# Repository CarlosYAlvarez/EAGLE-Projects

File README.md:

# EAGLE-Projects
Personal EAGLE Projects

# SimpleDuino
Arduino circuit on breadboard version.
References: https://circuitdigest.com/microcontroller-projects/how-to-burn-bootloader-in-atmega328p-and-program-using-arduino-ide

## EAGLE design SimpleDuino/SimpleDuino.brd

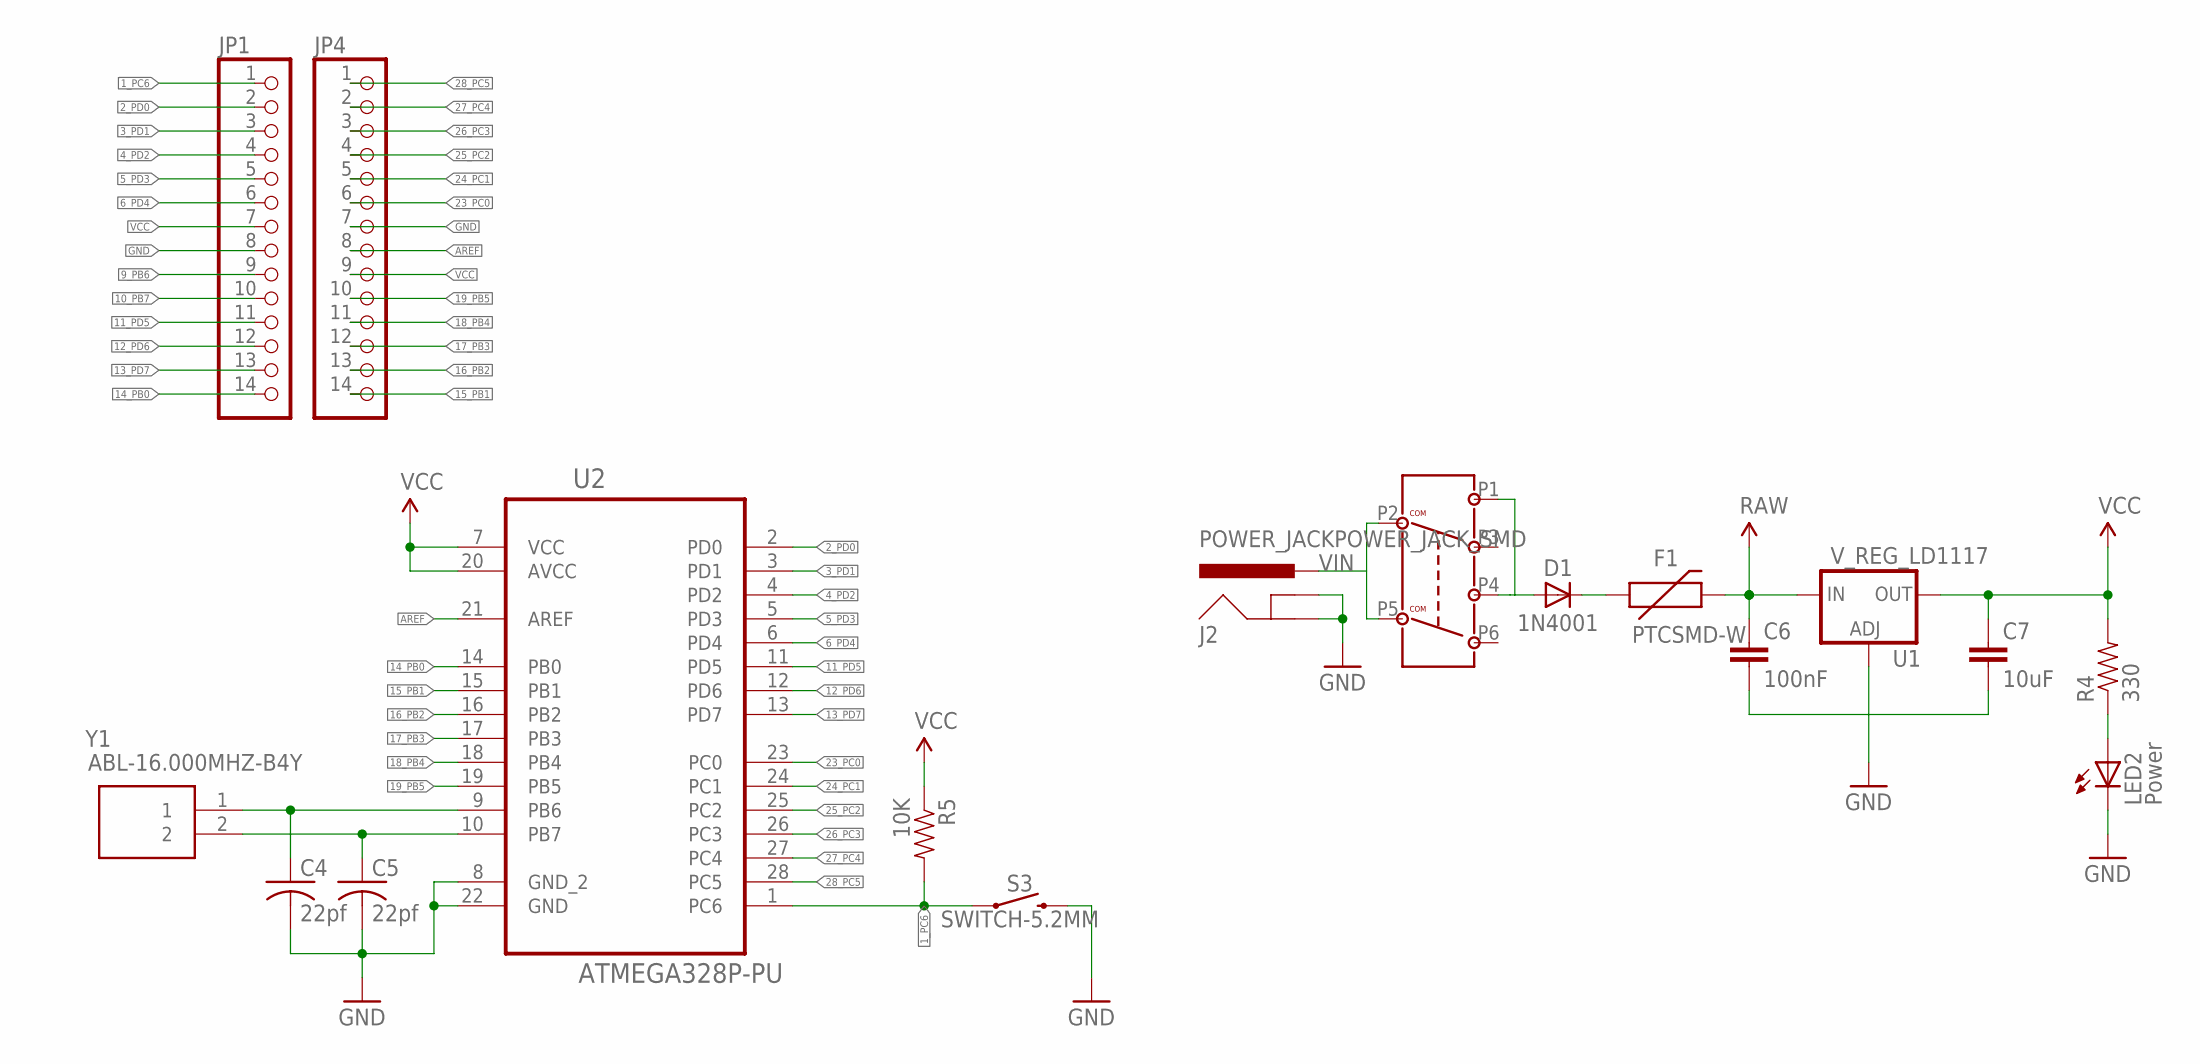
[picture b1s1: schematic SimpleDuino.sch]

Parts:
C4, C5: 22pf; C0805
C6: 100nF; 0603-CAP
C7: 10uF; 0603-CAP
D1: 1N4001; DO41-10
F1: PTCSMD-W; PTC-1206-WIDE
J2: POWER_JACKPOWER_JACK_SMD; POWER_JACK_SMD
JP1, JP4: PINHD-1X14; 1X14
LED2: Power; LED-1206
POWER_SWITCH: 6-PIN-SLIDE-SWITCH
R4: 330; 0603-RES
R5: 10K; 0603-RES
S3: SWITCH-5.2MM; TACTILE_SWITCH_SMD_5.2MM
U1: V_REG_LD1117; SOT223
U2: ATMEGA328P-PU; DIP254P762X457-28
Y1: ABL-16.000MHZ-B4Y; HC/49US_(AT49)PTH

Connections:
1_PC6: JP1.1, R5.2, S3.1, U2.1 (PC6)
2_PD0: JP1.2, U2.2 (PD0)
3_PD1: JP1.3, U2.3 (PD1)
4_PD2: JP1.4, U2.4 (PD2)
5_PD3: JP1.5, U2.5 (PD3)
6_PD4: JP1.6, U2.6 (PD4)
9_PB6: C4.1, JP1.9, U2.9 (PB6), Y1.1
10_PB7: C5.1, JP1.10, U2.10 (PB7), Y1.2
11_PD5: JP1.11, U2.11 (PD5)
12_PD6: JP1.12, U2.12 (PD6)
13_PD7: JP1.13, U2.13 (PD7)
14_PB0: JP1.14, U2.14 (PB0)
15_PB1: JP4.14, U2.15 (PB1)
16_PB2: JP4.13, U2.16 (PB2)
17_PB3: JP4.12, U2.17 (PB3)
18_PB4: JP4.11, U2.18 (PB4)
19_PB5: JP4.10, U2.19 (PB5)
23_PC0: JP4.6, U2.23 (PC0)
24_PC1: JP4.5, U2.24 (PC1)
25_PC2: JP4.4, U2.25 (PC2)
26_PC3: JP4.3, U2.26 (PC3)
27_PC4: JP4.2, U2.27 (PC4)
28_PC5: JP4.1, U2.28 (PC5)
AREF: JP4.8, U2.21 (AREF)
GND: C4.2, C5.2, C6.2, C7.2, J2.GND, J2.P$4 (GNDBREAK), JP1.8, JP4.7, LED2.C, S3.3 (2), U1.1 (ADJ), U2.8 (GND_2), U2.22 (GND)
unnamed: D1.C, F1.1
unnamed: LED2.A, R4.1
unnamed: D1.A, POWER_SWITCH.P1 (1), POWER_SWITCH.P4 (4)
RAW: C6.1, F1.2, U1.3 (IN)
VCC: C7.1, JP1.7, JP4.9, R4.2, R5.1, U1.2 (OUT), U2.7 (VCC), U2.20 (AVCC)
VIN: J2.VIN0 (PWR), POWER_SWITCH.P2 (2), POWER_SWITCH.P5 (5)

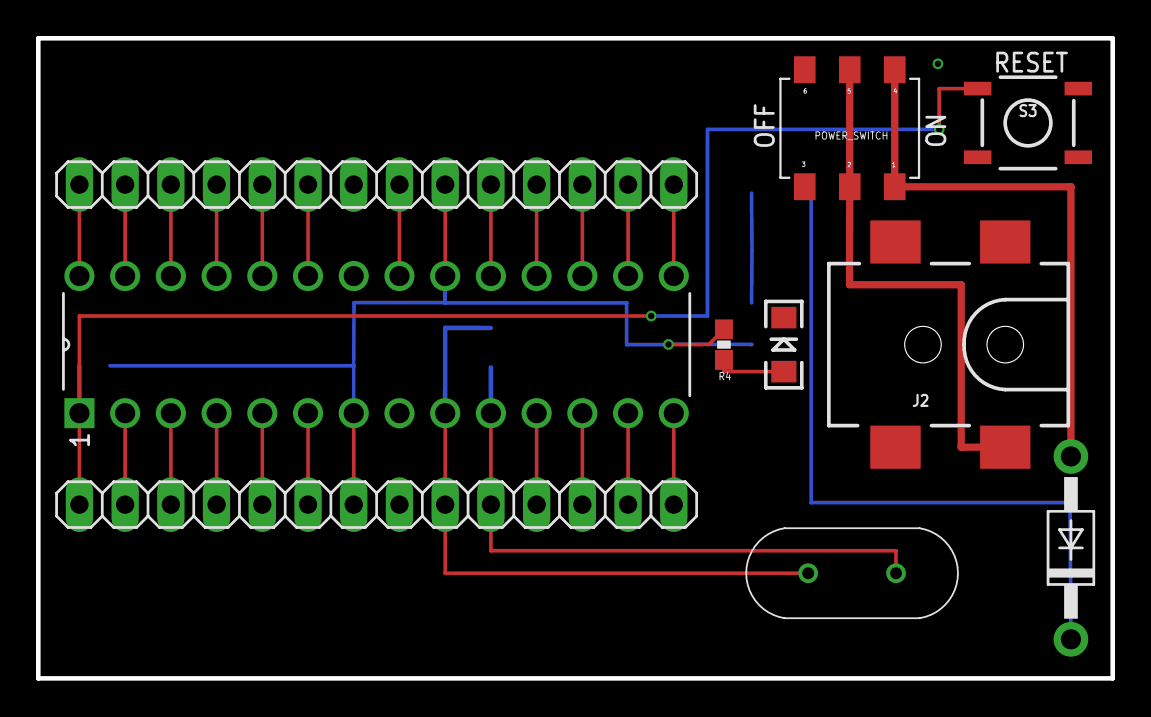
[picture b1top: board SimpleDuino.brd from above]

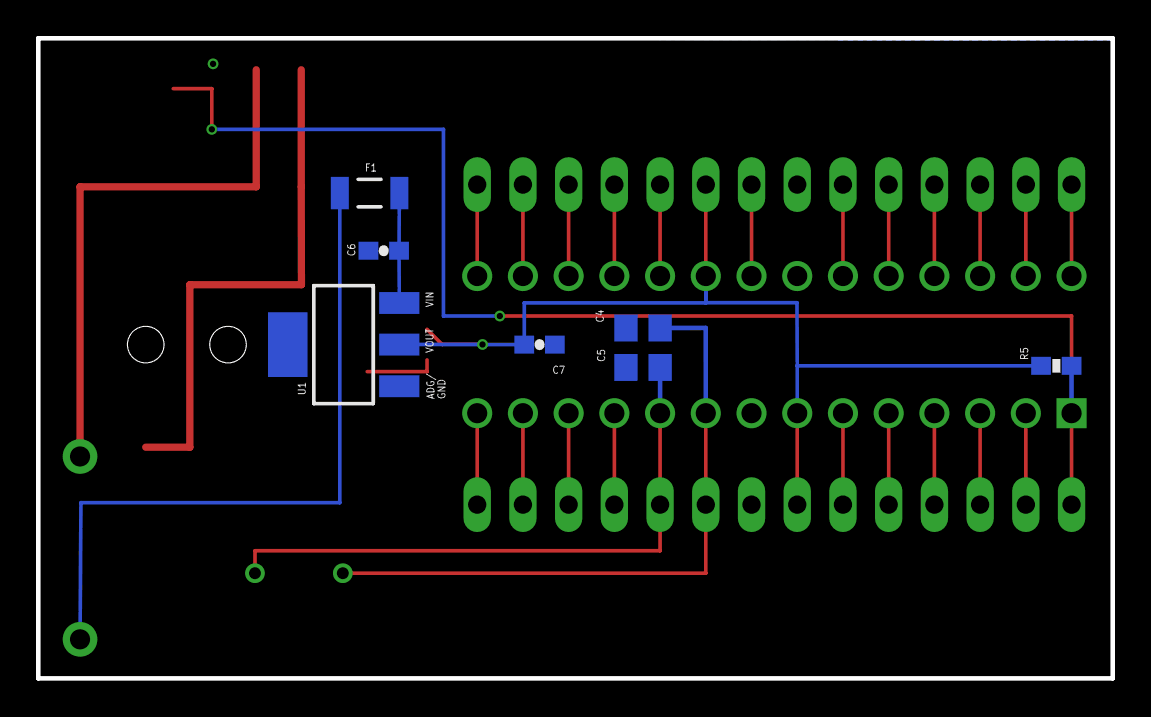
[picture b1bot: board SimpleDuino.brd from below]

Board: 2 copper layers, 59.7 x 35.6 mm, 17 parts (7 on the bottom side), 31 nets.

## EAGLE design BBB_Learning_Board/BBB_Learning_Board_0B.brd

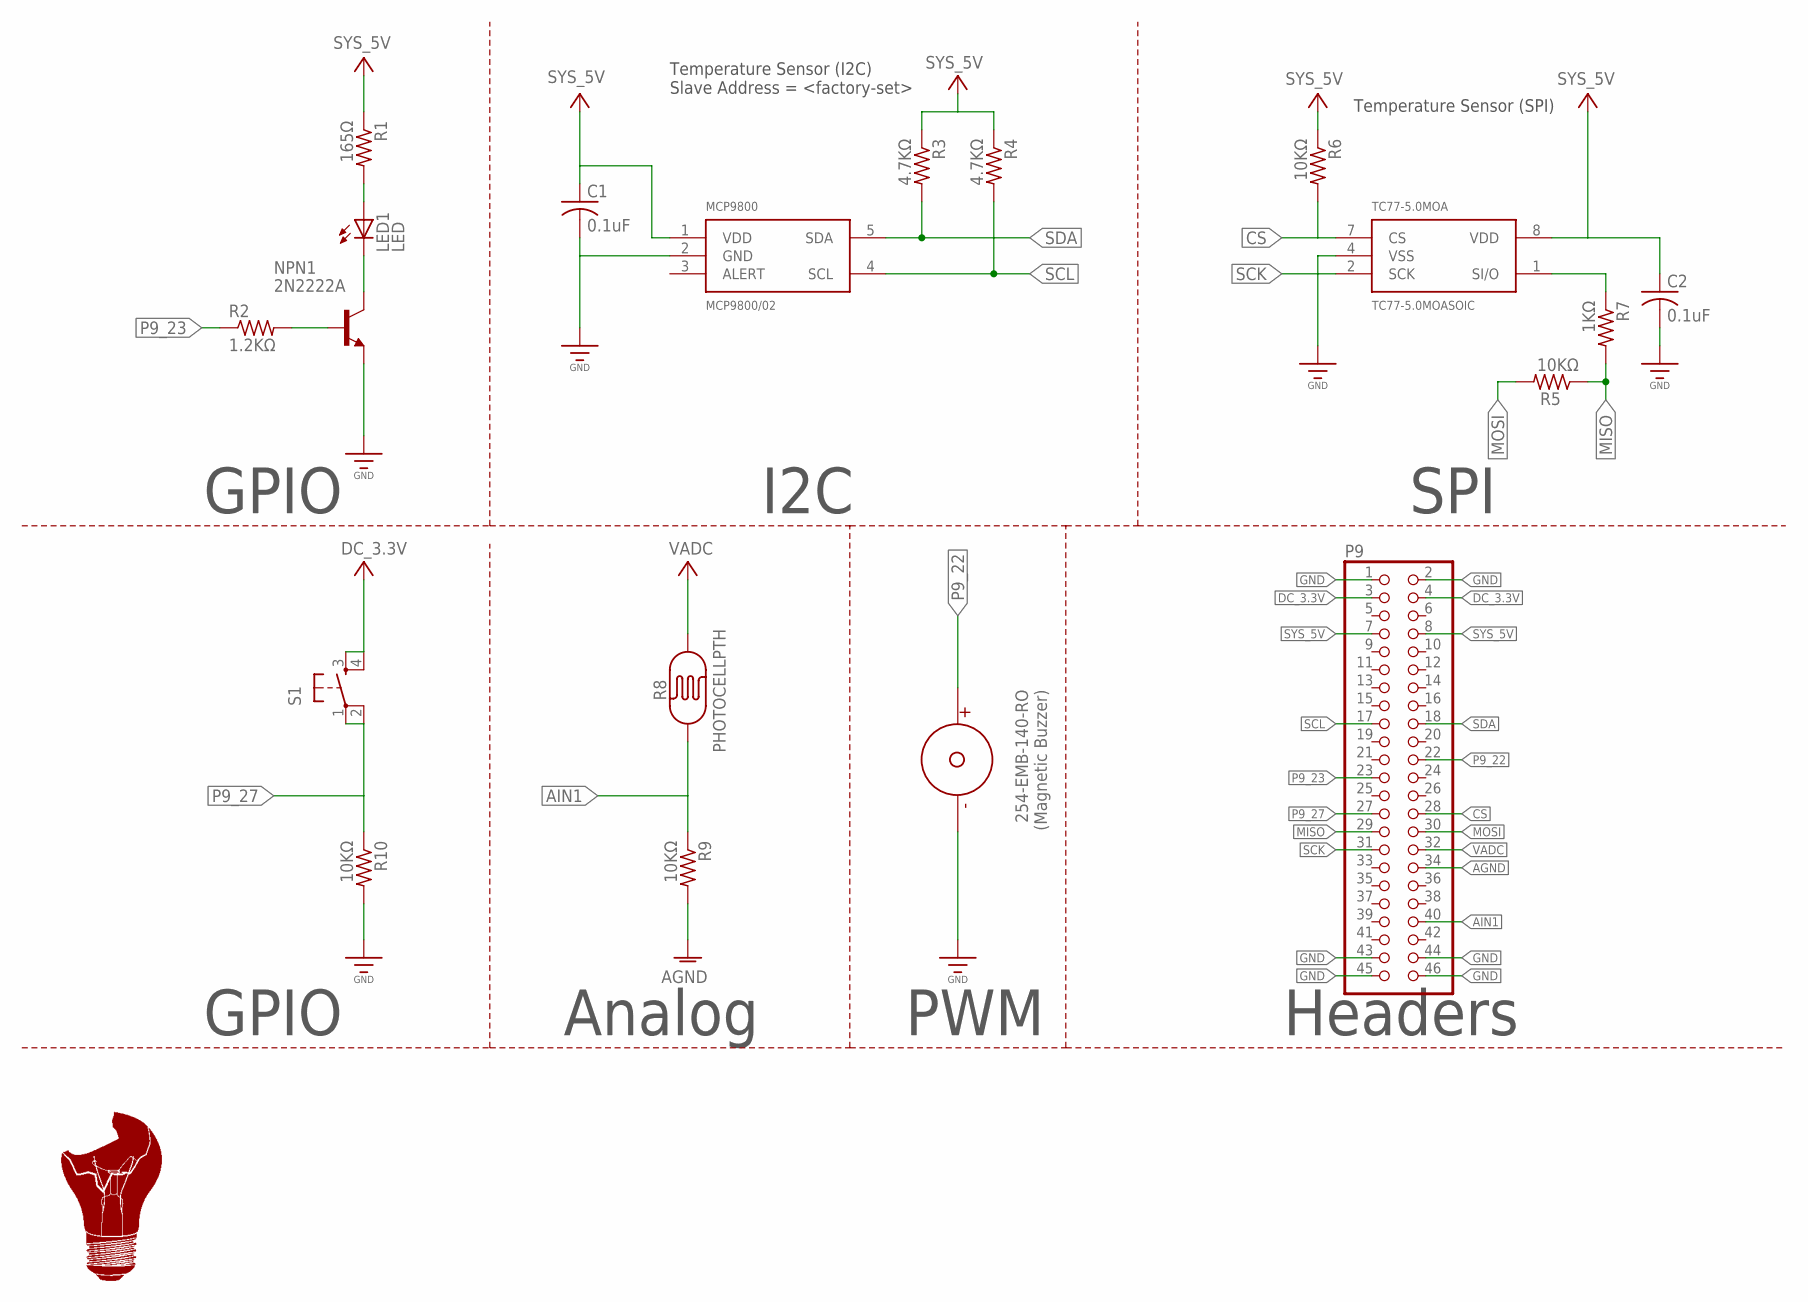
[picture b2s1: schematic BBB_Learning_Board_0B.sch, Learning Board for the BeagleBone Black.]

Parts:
C1, C2: 0.1uF; C0805
LED1: LED; LED5MM
MCP9800: MCP9800/02; SOT23-5
NPN1: 2N2222A; PINHD-1X3
P9: PINHD-2X23; 2X23
R1: 165Ω; R0805
R2: 1.2KΩ; R0805
R3, R4: 4.7KΩ; R0805
R5, R6, R9, R10: 10KΩ; R0805
R7: 1KΩ; R0805
R8: PHOTOCELLPTH; PHOTOCELL
S1: TAC_SWITCHPTH; TACTILE-PTH
TC77-5.0MOA: TC77-5.0MOASOIC; SOIC-8
U$6: 254-EMB-140-RO
U$7: LIGHTBULB_LOGOBOTTOM; LIGHTBULB_LOGO_BOTTOM-2_54CM2

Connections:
AGND: P9.34, R9.2
AIN1: P9.40, R8.1, R9.1
CS: P9.28, R6.2, TC77-5.0MOA.7 (CS)
DC_3.3V: P9.3, P9.4, S1.3, S1.4
GND: C1.2, C2.2, MCP9800.2 (GND), NPN1.1 (E), P9.1, P9.2, P9.43, P9.44, P9.45, P9.46, R10.2, TC77-5.0MOA.4 (VSS), U$6.NEGATIVE
MISO: P9.29, R5.1, R7.2
MOSI: P9.30, R5.2
unnamed: LED1.ANODE (A), R1.2
unnamed: NPN1.2 (B), R2.2
unnamed: LED1.CATHODE (C), NPN1.3 (C)
P9_22: P9.22, U$6.POSITIVE
P9_23: P9.23, R2.1
P9_27: P9.27, R10.1, S1.1, S1.2
SCK: P9.31, TC77-5.0MOA.2 (SCK)
SCL: MCP9800.4 (SCL), P9.17, R4.2
SDA: MCP9800.5 (SDA), P9.18, R3.2
SI/O: R7.1, TC77-5.0MOA.1 (SI/O)
SYS_5V: C1.1, C2.1, MCP9800.1 (VDD), P9.7, P9.8, R1.1, R3.1, R4.1, R6.1, TC77-5.0MOA.8 (VDD)
VADC: P9.32, R8.2

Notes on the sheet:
Temperature Sensor (I2C) Slave Address = <factory-set>
Temperature Sensor (SPI)
GPIO
I2C
SPI
Analog
PWM
Headers

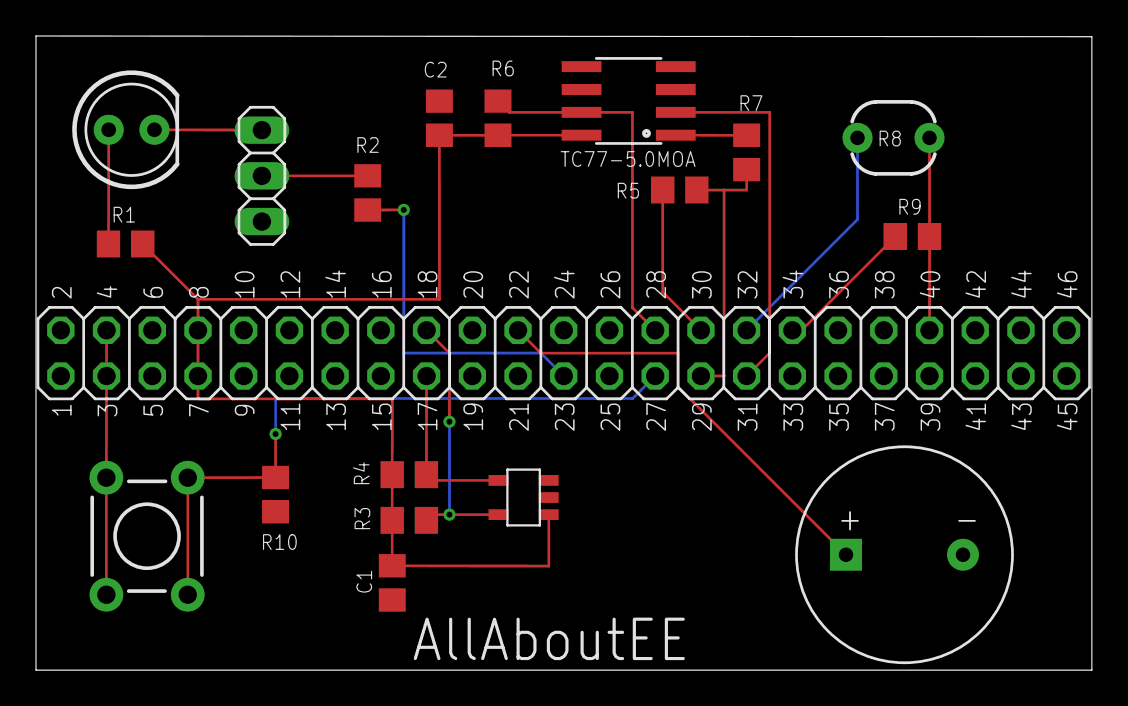
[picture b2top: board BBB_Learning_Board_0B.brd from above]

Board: 2 copper layers, 58.7 x 35.2 mm, 20 parts (0 on the bottom side), 19 nets.

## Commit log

2020-08-15 Version 1 of APA102 PCB.
2020-08-24 Updated design to use the 6-pin header autogenerated from Library.IO that includes a 3D package.
2020-08-24 Updated .gitignore to ignore *.s#* files.
2020-09-14 Updated to include devices containing 3D Objects for crystal and power jack.
2022-06-05 Moved BeagleBoneBlackLearningBoard files into new repo.
2022-06-05 Duplicated APA102_Arduino project to use as a base for Arduino bootloader circuit.
2022-06-05 Added description for: SimpleDuino project
2022-06-23 Included BOM for APA102
    "Headers & Wire Housings 6P 1ROW STRT SOCKET" can be ignored for this project.
2022-06-25 Controlled BOM for APA102 project.
2022-06-25 Renamed BOM for SimpleDuino.
2022-06-25 Replacing Mouser#:650-NANOSMD400LR-C-2 (Fuse) with 576-1206L400/12SLWR. Previous part no longer exists.
2022-06-25 Adde new part 621-AZ1117H-5.0TRG1 since original voltage regulator is not available.
2022-06-25 Added replacement for 16MHz Crystal.
2022-08-28 Added additional headers and restructured pcb layout.

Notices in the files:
parts and their libraries:
SparkFun-Sensors: Licensing: Creative Commons ShareAlike 4.0 International - https://creativecommons.org/licenses/by-sa/4.0
SparkFun-PowerIC: Licensing: CC v3.0 Share-Alike You are welcome to use this library for commercial purposes.
